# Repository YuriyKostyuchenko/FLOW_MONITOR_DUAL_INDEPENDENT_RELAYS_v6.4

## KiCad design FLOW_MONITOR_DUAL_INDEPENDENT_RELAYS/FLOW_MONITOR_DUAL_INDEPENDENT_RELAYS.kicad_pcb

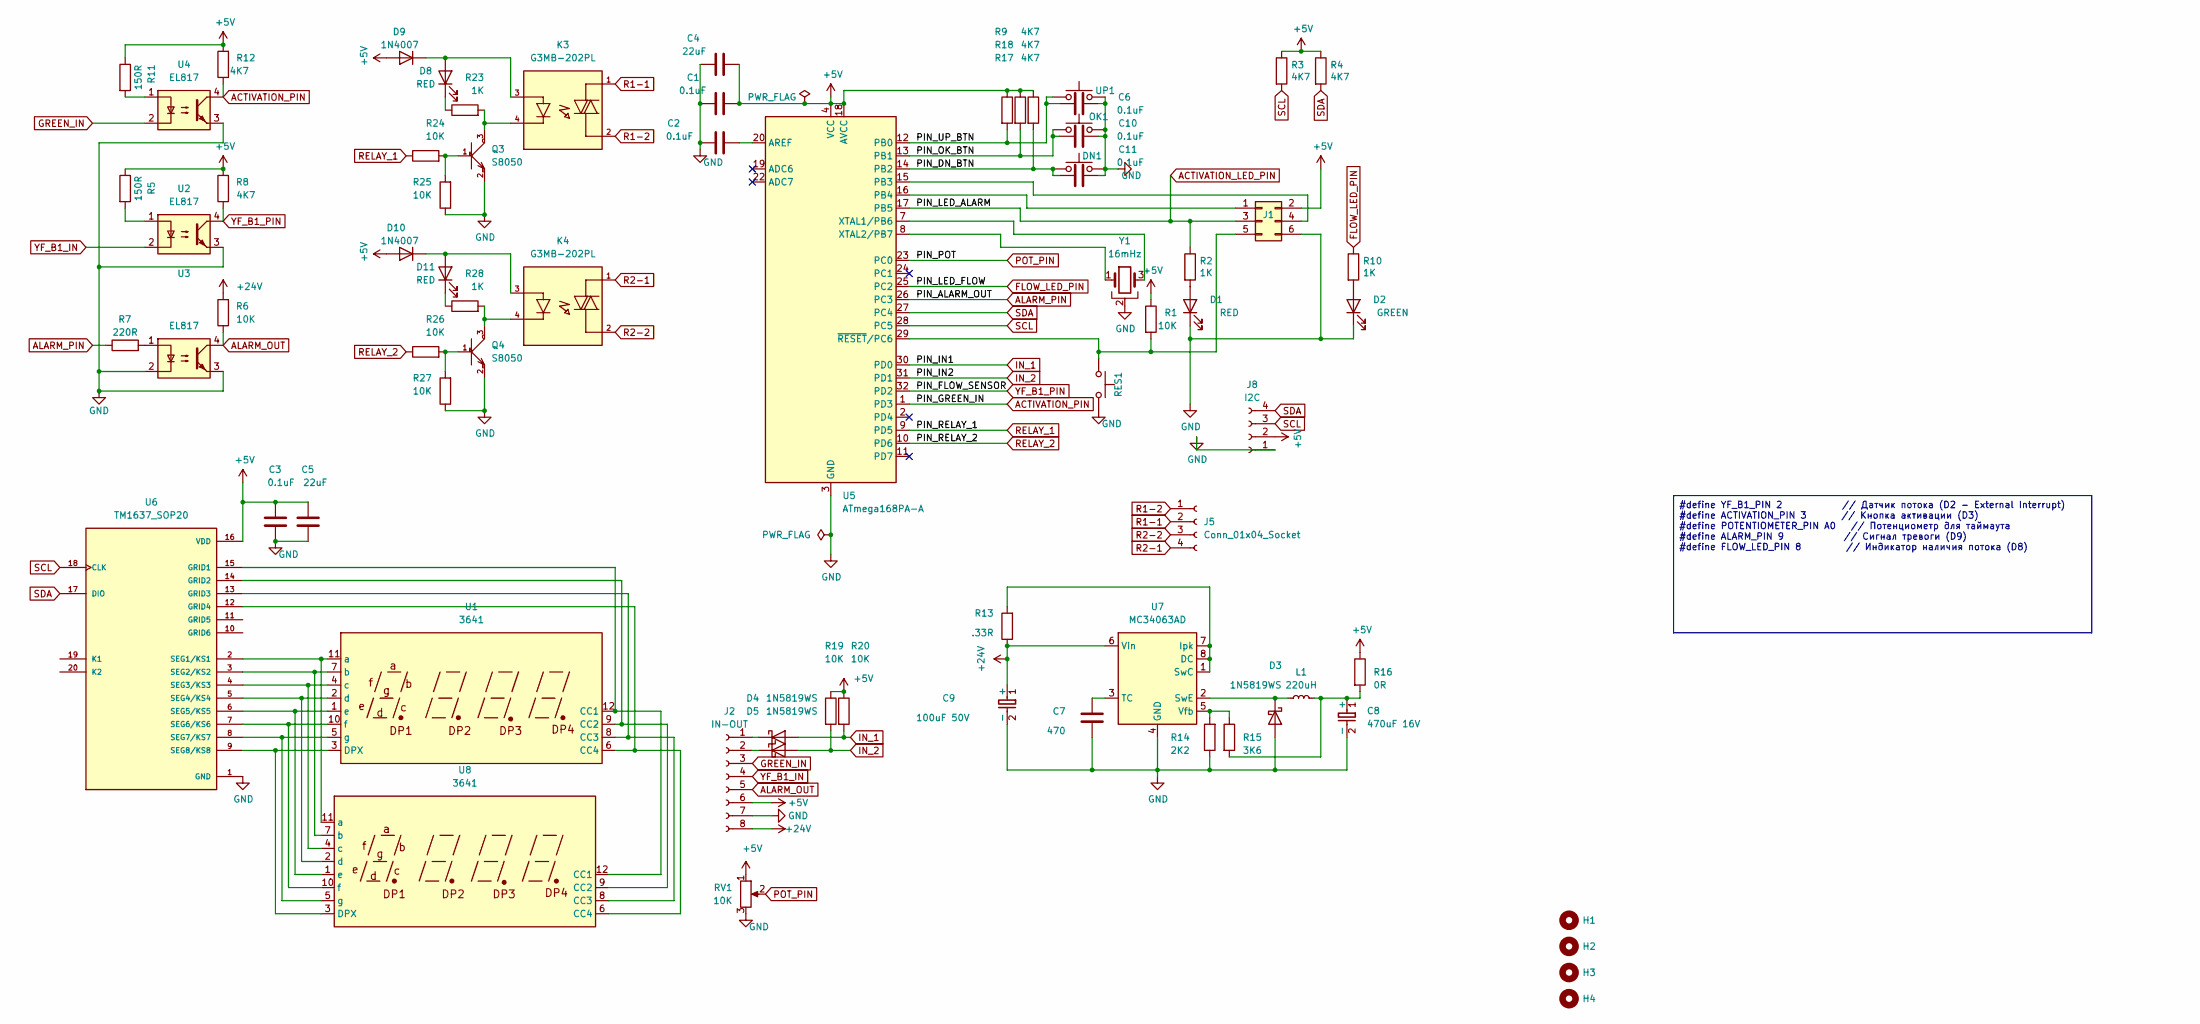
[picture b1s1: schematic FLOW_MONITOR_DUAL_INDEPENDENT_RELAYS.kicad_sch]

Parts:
C1, C2, C3, C6, C10, C11: 0.1uF; C_0805_2012Metric_Pad1.18x1.45mm_HandSolder
C4: 22uF; C_1206_3216Metric_Pad1.33x1.80mm_HandSolder
C5: 22uF; C_0805_2012Metric_Pad1.18x1.45mm_HandSolder
C7: 470; C_0805_2012Metric_Pad1.18x1.45mm_HandSolder
C8: 470uF 16V; CP_Elec_10x10.5
C9: 100uF 50V; CP_Elec_8x10
D1, D8, D11: RED; LED_0805_2012Metric_Pad1.15x1.40mm_HandSolder
D2: GREEN; LED_0805_2012Metric_Pad1.15x1.40mm_HandSolder
D3, D4, D5: 1N5819WS; D_SOD-123
D9, D10: 1N4007; D_SMA
DN1: SW_Push; SW_PUSH_6mm
H1, H2, H3, H4: MountingHole; MountingHole_2.5mm
J1: Conn_02x03_Top_Bottom; PinHeader_2x03_P2.54mm_Vertical
J2: IN-OUT; PhoenixContact_MCV_1,5_8-G-3.81_1x08_P3.81mm_Vertical
J5: Conn_01x04_Socket; PhoenixContact_MCV_1,5_4-G-3.81_1x04_P3.81mm_Vertical
J8: I2C; OLED_LCD_128x32
K3, K4: G3MB-202PL; RELAY_G3MB-202PL; PARTREV 06/09
L1: 220uH; L_7.3x7.3_!!!!!!!
OK1: SW_Push; SW_PUSH_6mm
Q3, Q4: S8050; SOT-23; MPN S8050
R1, R6, R19, R20, R24, R25, R26, R27: 10K; R_0805_2012Metric_Pad1.20x1.40mm_HandSolder
R2, R10, R23, R28: 1K; R_0805_2012Metric_Pad1.20x1.40mm_HandSolder
R3, R4, R8, R9, R12, R17, R18: 4K7; R_0805_2012Metric_Pad1.20x1.40mm_HandSolder
R5, R11: 150R; R_0805_2012Metric_Pad1.20x1.40mm_HandSolder
R7: 220R; R_0805_2012Metric_Pad1.20x1.40mm_HandSolder
R13: .33R; R_0805_2012Metric_Pad1.20x1.40mm_HandSolder
R14: 2K2; R_0805_2012Metric_Pad1.20x1.40mm_HandSolder
R15: 3K6; R_0805_2012Metric_Pad1.20x1.40mm_HandSolder
R16: 0R; R_0805_2012Metric_Pad1.20x1.40mm_HandSolder
RES1: SW_Push; SW_Tactile_SPST_NO_Straight_CK_PTS636Sx25SMTRLFS
RV1: 10K; Potentiometer_Bourns_3314J_Vertical
U1: 3641; 3631
U2, U3, U4: EL817; DIP-4_W7.62mm
U5: ATmega168PA-A; TQFP-32_7x7mm_P0.8mm
U6: TM1637_SOP20; SOIC127P1035X255-20N; PARTREV V2.6
U7: MC34063AD; SOIC-8_3.9x4.9mm_P1.27mm
U8: 3641; CC56-12GWA
UP1: SW_Push; SW_PUSH_6mm
Y1: 16mHz; XTAL_ZTT-4.00MG

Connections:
+5V: C1.2, C3.2, C4.2, C5.2, D9.2 (A), D10.2 (A), J1.2, J2.6, J8.2, R1.1, R3.1, R4.1, R5.1, R8.2, R9.1, R11.1, R12.2, R16.1, R17.1, R18.1, R19.1, R20.1, RV1.1, U5.4 (VCC), U5.6 (VCC), U5.18 (AVCC), U6.16 (VDD)
+24V: C9.1 (+), J2.8, R6.2, R13.1, U7.6 (Vin)
ACTIVATION_LED_PIN: J1.3, R2.1, U5.17 (PB5)
ACTIVATION_PIN: R12.1, U4.4, U5.1 (PD3)
ALARM_OUT: J2.5, R6.1, U3.4
ALARM_PIN: R7.1, U5.26 (PC3)
FLOW_LED_PIN: R10.1, U5.25 (PC2)
GND: C1.1, C2.1, C3.1, C4.1, C5.1, C6.2, C7.1, C8.2 (-), C9.2 (-), C10.2, C11.2, D1.1 (K), D2.1 (K), D3.2 (A), DN1.2, J1.6, J2.7, J8.1, OK1.2, Q3.2, Q4.2, R14.1, R25.1, R27.1, RES1.2, RV1.3, U2.3, U3.2, U3.3, U4.3, U5.3 (GND), U5.5 (GND), U5.21 (GND), U6.1 (GND), U7.4 (GND), UP1.2, Y1.2
GREEN_IN: J2.3, U4.2
IN_1: D4.2 (A), R20.2, U5.30 (PD0)
IN_2: D5.2 (A), R19.2, U5.31 (PD1)
unnamed: C8.1 (+), L1.2, R15.2, R16.2
unnamed: D1.2 (A), R2.2
unnamed: D2.2 (A), R10.2
unnamed: D3.1 (K), L1.1, U7.2 (SwE)
unnamed: D4.1 (K), J2.1
unnamed: D5.1 (K), J2.2
unnamed: D8.2 (A), D9.1 (K), K3.3
unnamed: D8.1 (K), R23.1
unnamed: D10.1 (K), D11.2 (A), K4.3
unnamed: D11.1 (K), R28.1
unnamed: J1.1, U5.16 (PB4)
unnamed: J1.4, U5.15 (PB3)
unnamed: J1.5, R1.2, RES1.1, U5.29 (~RESET/PC6)
unnamed: K3.4, Q3.3, R23.2
unnamed: K4.4, Q4.3, R28.2
unnamed: Q3.1, R24.2, R25.2
unnamed: Q4.1, R26.2, R27.2
unnamed: R5.2, U2.1
unnamed: R7.2, U3.1
unnamed: R11.2, U4.1
unnamed: U1.12 (CC1), U6.15 (GRID1), U8.12 (CC1)
unnamed: U1.9 (CC2), U6.14 (GRID2), U8.9 (CC2)
unnamed: U1.8 (CC3), U6.13 (GRID3), U8.8 (CC3)
unnamed: U1.6 (CC4), U6.12 (GRID4), U8.6 (CC4)
unnamed: U1.3 (DPX), U6.9 (SEG8/KS8), U8.3 (DPX)
unnamed: U1.11 (a), U6.2 (SEG1/KS1), U8.11 (a)
unnamed: U1.7 (b), U6.3 (SEG2/KS2), U8.7 (b)
unnamed: U1.4 (c), U6.4 (SEG3/KS3), U8.4 (c)
unnamed: U1.2 (d), U6.5 (SEG4/KS4), U8.2 (d)
unnamed: U1.1 (e), U6.6 (SEG5/KS5), U8.1 (e)
unnamed: U1.10 (f), U6.7 (SEG6/KS6), U8.10 (f)
unnamed: U1.5 (g), U6.8 (SEG7/KS7), U8.5 (g)
unnamed: C2.2, U5.20 (AREF)
unnamed: C6.1, R9.2, U5.12 (PB0), UP1.1
unnamed: C10.1, OK1.1, R17.2, U5.13 (PB1)
unnamed: C11.1, DN1.1, R18.2, U5.14 (PB2)
unnamed: U5.7 (XTAL1/PB6), Y1.3
unnamed: U5.8 (XTAL2/PB7), Y1.1
unnamed: R13.2, U7.1 (SwC), U7.7 (Ipk), U7.8 (DC)
unnamed: C7.2, U7.3 (TC)
unnamed: R14.2, R15.1, U7.5 (Vfb)
POT_PIN: RV1.2, U5.23 (PC0)
R1-1: J5.2, K3.1
R1-2: J5.1, K3.2
R2-1: J5.4, K4.1
R2-2: J5.3, K4.2
RELAY_1: R24.1, U5.9 (PD5)
RELAY_2: R26.1, U5.10 (PD6)
SCL: J8.3, R3.2, U5.28 (PC5), U6.18 (CLK)
SDA: J8.4, R4.2, U5.27 (PC4), U6.17 (DIO)
YF_B1_IN: J2.4, U2.2
YF_B1_PIN: R8.1, U2.4, U5.32 (PD2)

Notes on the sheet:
#define YF_B1_PIN 2 // Датчик потока (D2 - External Interrupt) #define ACTIVATION_PIN 3 // Кнопка активации (D3) #define POTENTIOMETER_PIN A0 // Потенциометр для таймаута #define ALARM_PIN 9 // Сигнал тревоги (D9) #define FLOW_LED_PIN 8 // Индикатор наличия потока (D8)

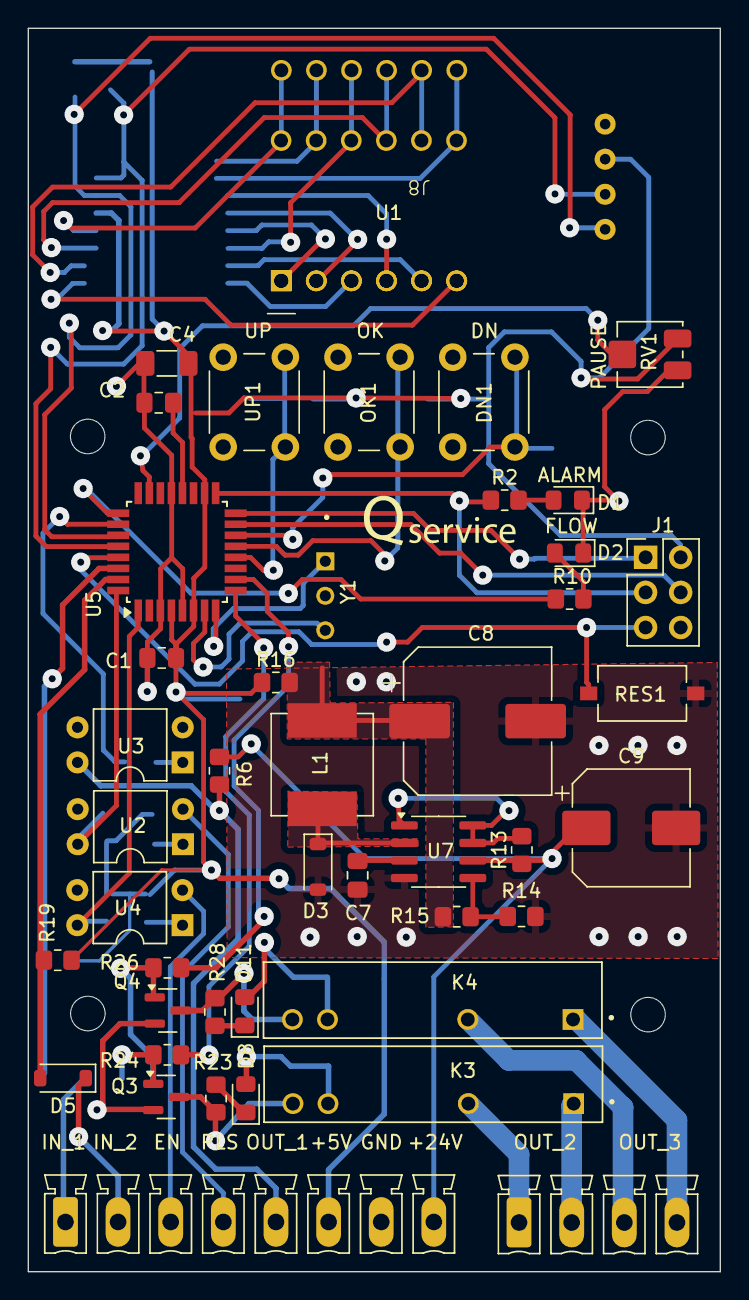
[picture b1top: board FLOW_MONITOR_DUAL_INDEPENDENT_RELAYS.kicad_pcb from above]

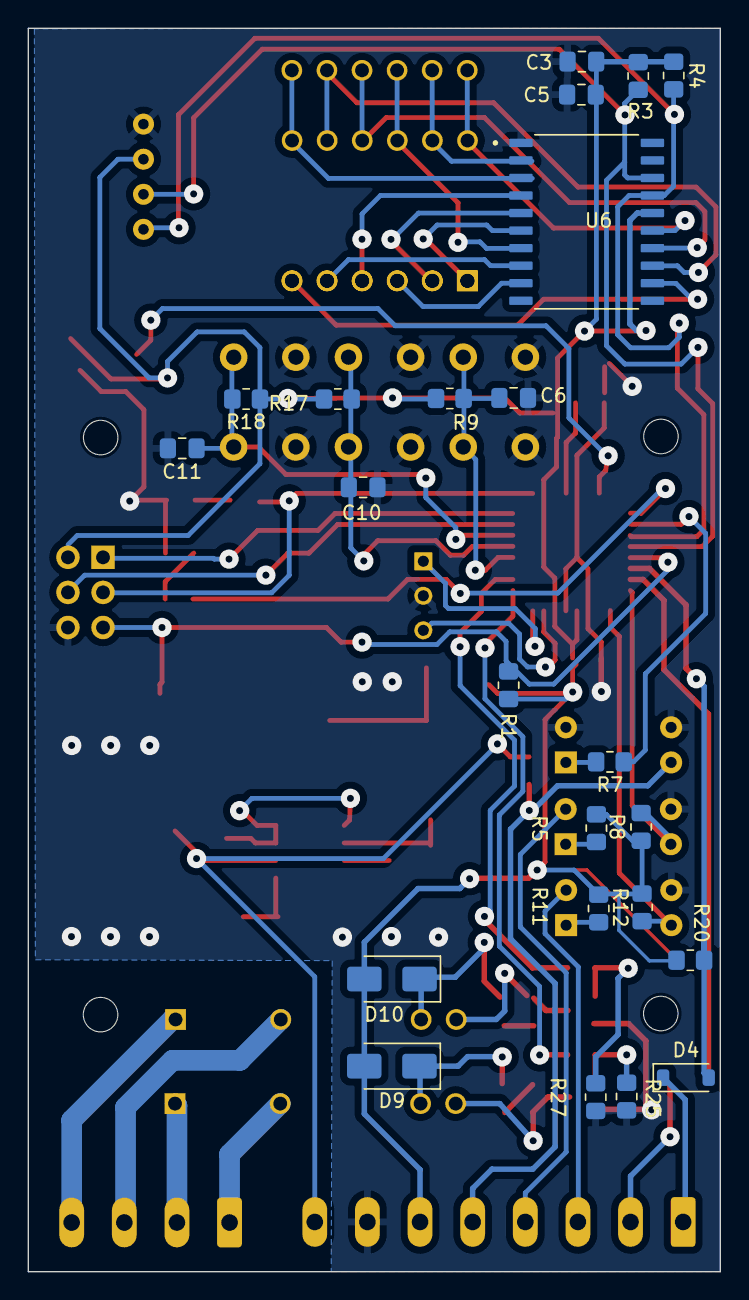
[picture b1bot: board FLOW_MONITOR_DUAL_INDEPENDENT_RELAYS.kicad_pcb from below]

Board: 2 copper layers, 50.1 x 90.0 mm, 73 parts (23 on the bottom side), 63 nets.

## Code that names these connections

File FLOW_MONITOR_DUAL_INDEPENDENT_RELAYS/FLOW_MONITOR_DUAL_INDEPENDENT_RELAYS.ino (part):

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#define PIN_DN_BTN      10  
#define PIN_LED_ALARM   13  
#define PIN_LED_FLOW    A2  
#define PIN_ALARM_OUT   A3  
#define PIN_IN1         0   
#define PIN_IN2         1   
#define PIN_FLOW_SENSOR 2   
#define PIN_GREEN_IN    3   
#define CLK             A5  
#define DIO             A4  
#define PIN_RELAY_1     5   
#define PIN_RELAY_2     6   

TM1637Display display(CLK, DIO);

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
void setup() {
  pinMode(PIN_OK_BTN, INPUT_PULLUP); pinMode(PIN_UP_BTN, INPUT_PULLUP); pinMode(PIN_DN_BTN, INPUT_PULLUP);
  pinMode(PIN_IN1, INPUT_PULLUP); pinMode(PIN_IN2, INPUT_PULLUP); pinMode(PIN_GREEN_IN, INPUT_PULLUP); 
  pinMode(PIN_FLOW_SENSOR, INPUT_PULLUP);
  pinMode(PIN_LED_ALARM, OUTPUT); pinMode(PIN_LED_FLOW, OUTPUT); pinMode(PIN_ALARM_OUT, OUTPUT);
  pinMode(PIN_RELAY_1, OUTPUT); pinMode(PIN_RELAY_2, OUTPUT);

  EEPROM.get(0, settings);
  // Если checkByte совпадает (например 0x63), блок IF пропускается и настройки остаются старыми
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      else currentFlow_x100 = (flowPulseSnapshot * 6000UL) / (unsigned long)settings.P1_Calib;
    }

    bool alarmActive = !digitalRead(PIN_GREEN_IN);
    if (alarmActive) {
      if (stabilizationStart == 0) stabilizationStart = millis();
      if (!stabilizationComplete && (millis() - stabilizationStart >= (uint32_t)settings.P3_Delay * 1000)) stabilizationComplete = true;
      if (stabilizationComplete) {
        bool flowOk = (settings.P1_Calib == 0) ? (flowPulseSnapshot >= settings.P2_MinFlow) : (currentFlow_x100 >= settings.P2_MinFlow);
        digitalWrite(PIN_LED_FLOW, flowOk); digitalWrite(PIN_LED_ALARM, !flowOk); digitalWrite(PIN_ALARM_OUT, !flowOk);
      }
    } else {
      stabilizationStart = 0; stabilizationComplete = false;
      digitalWrite(PIN_LED_FLOW, LOW); digitalWrite(PIN_LED_ALARM, LOW); digitalWrite(PIN_ALARM_OUT, LOW);
    }
    display.showNumberDecEx(min(currentFlow_x100, 9999), (settings.P1_Calib > 0 ? 0x40 : 0), true);
  } else drawMenu();
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  uint16_t mode = (id == 1) ? settings.P4_R1Mode : settings.P7_R2Mode;
  uint32_t tA = (id == 1) ? (uint32_t)settings.P5_R1TimeA * 1000 : (uint32_t)settings.P8_R2TimeA * 1000;
  uint32_t tB = (id == 1) ? (uint32_t)settings.P6_R1TimeB * 1000 : (uint32_t)settings.P9_R2TimeB * 1000;
  int pin = (id == 1) ? PIN_RELAY_1 : PIN_RELAY_2;

  switch (mode) {
    case 0: digitalWrite(pin, !inVal); break;
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
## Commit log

2026-01-07 schematic & code
2026-01-07 manual
